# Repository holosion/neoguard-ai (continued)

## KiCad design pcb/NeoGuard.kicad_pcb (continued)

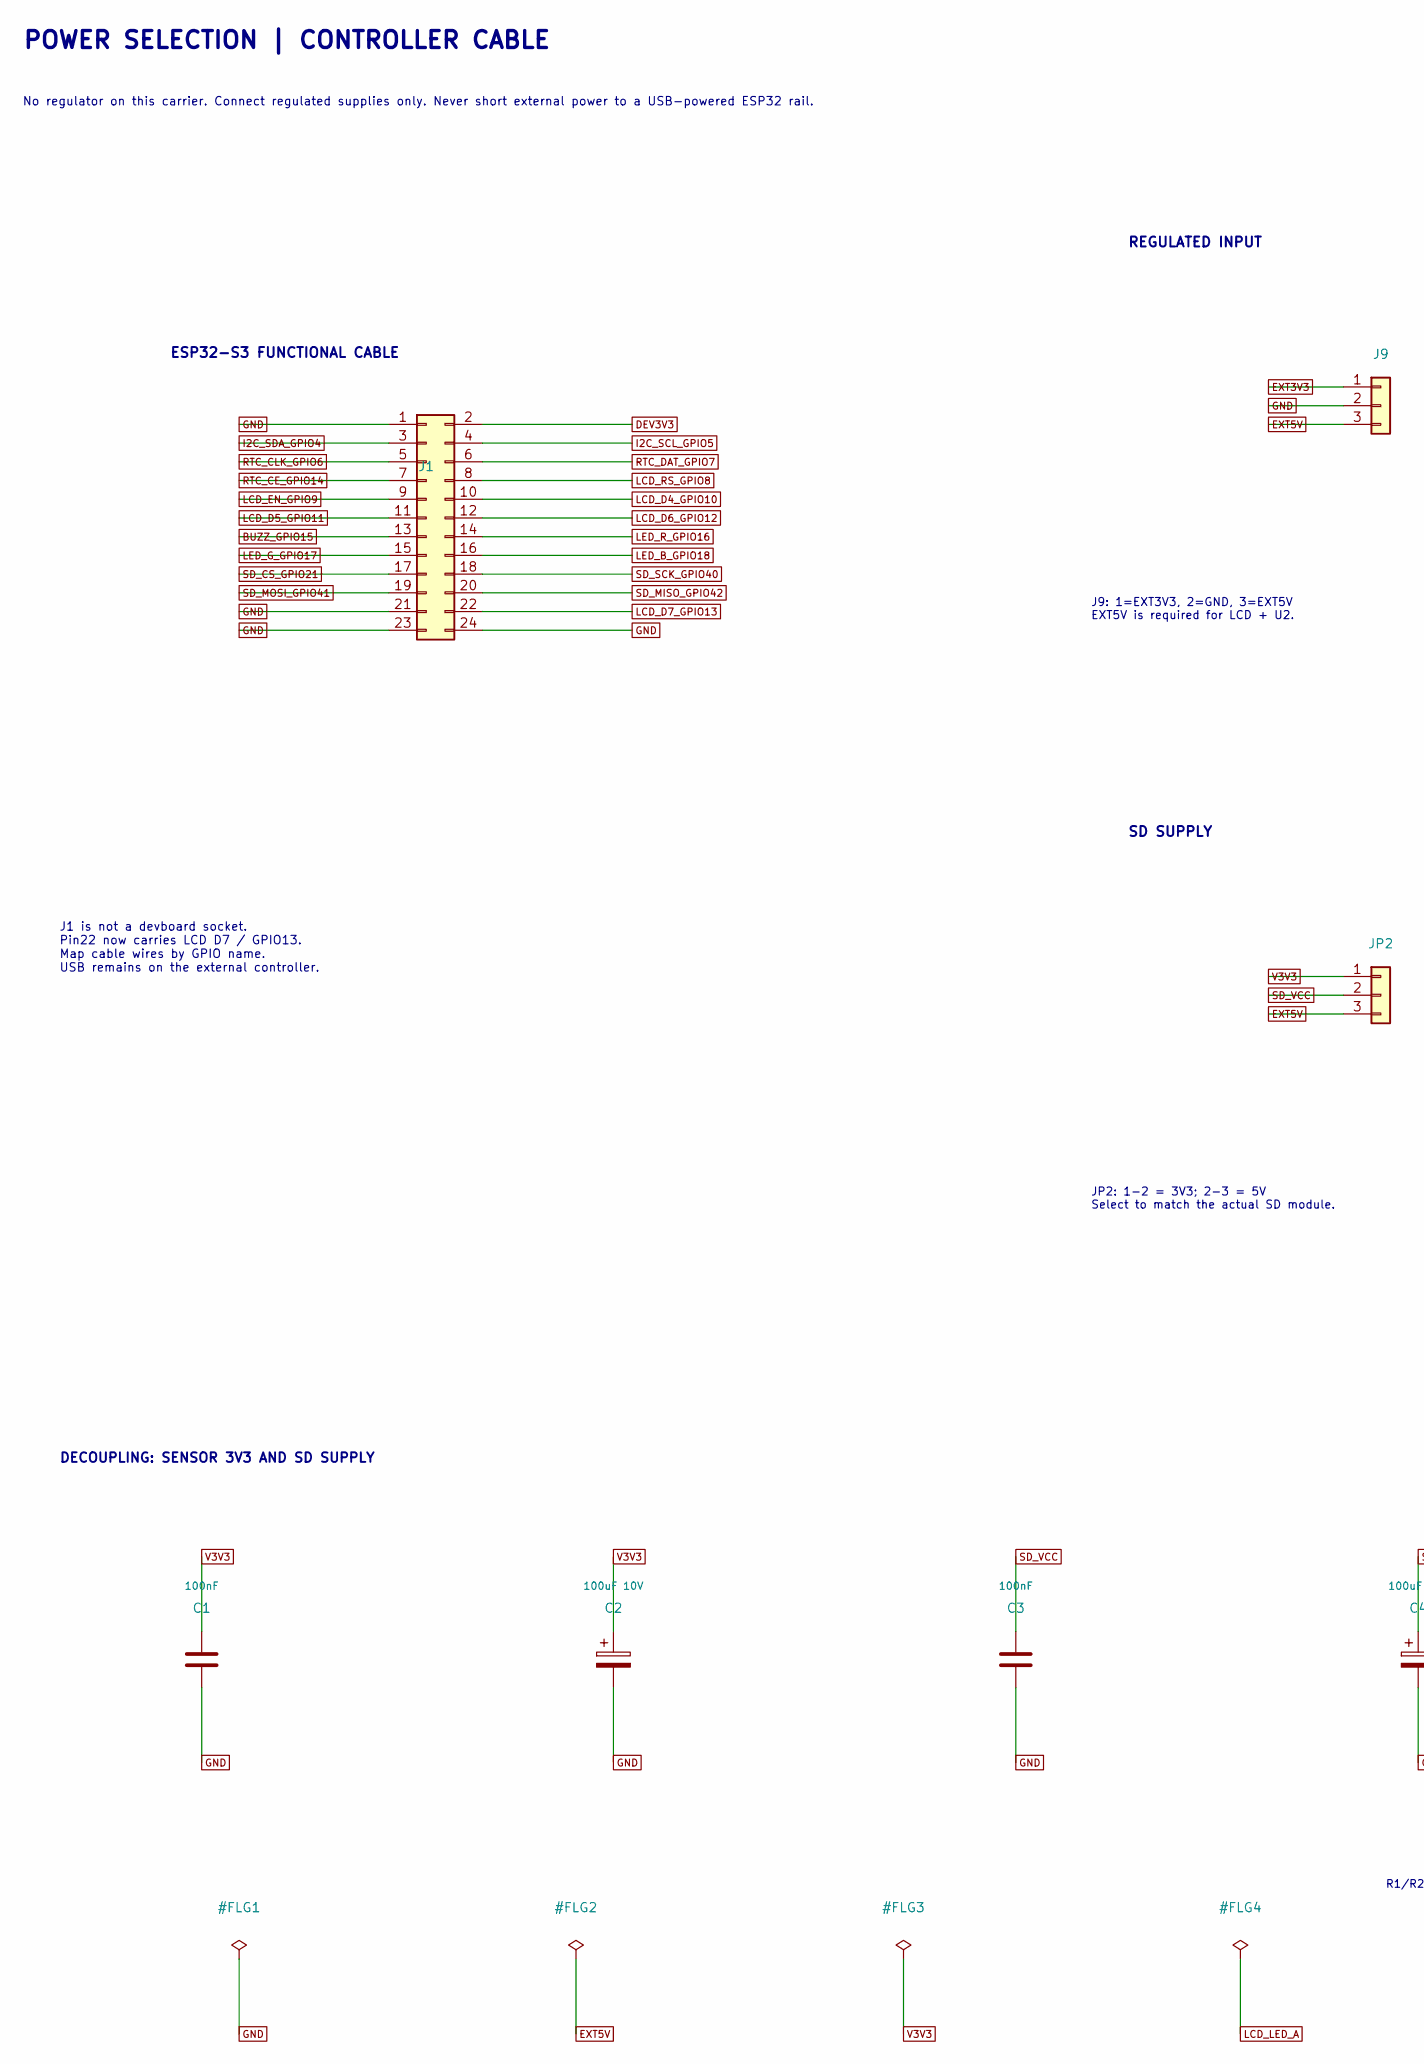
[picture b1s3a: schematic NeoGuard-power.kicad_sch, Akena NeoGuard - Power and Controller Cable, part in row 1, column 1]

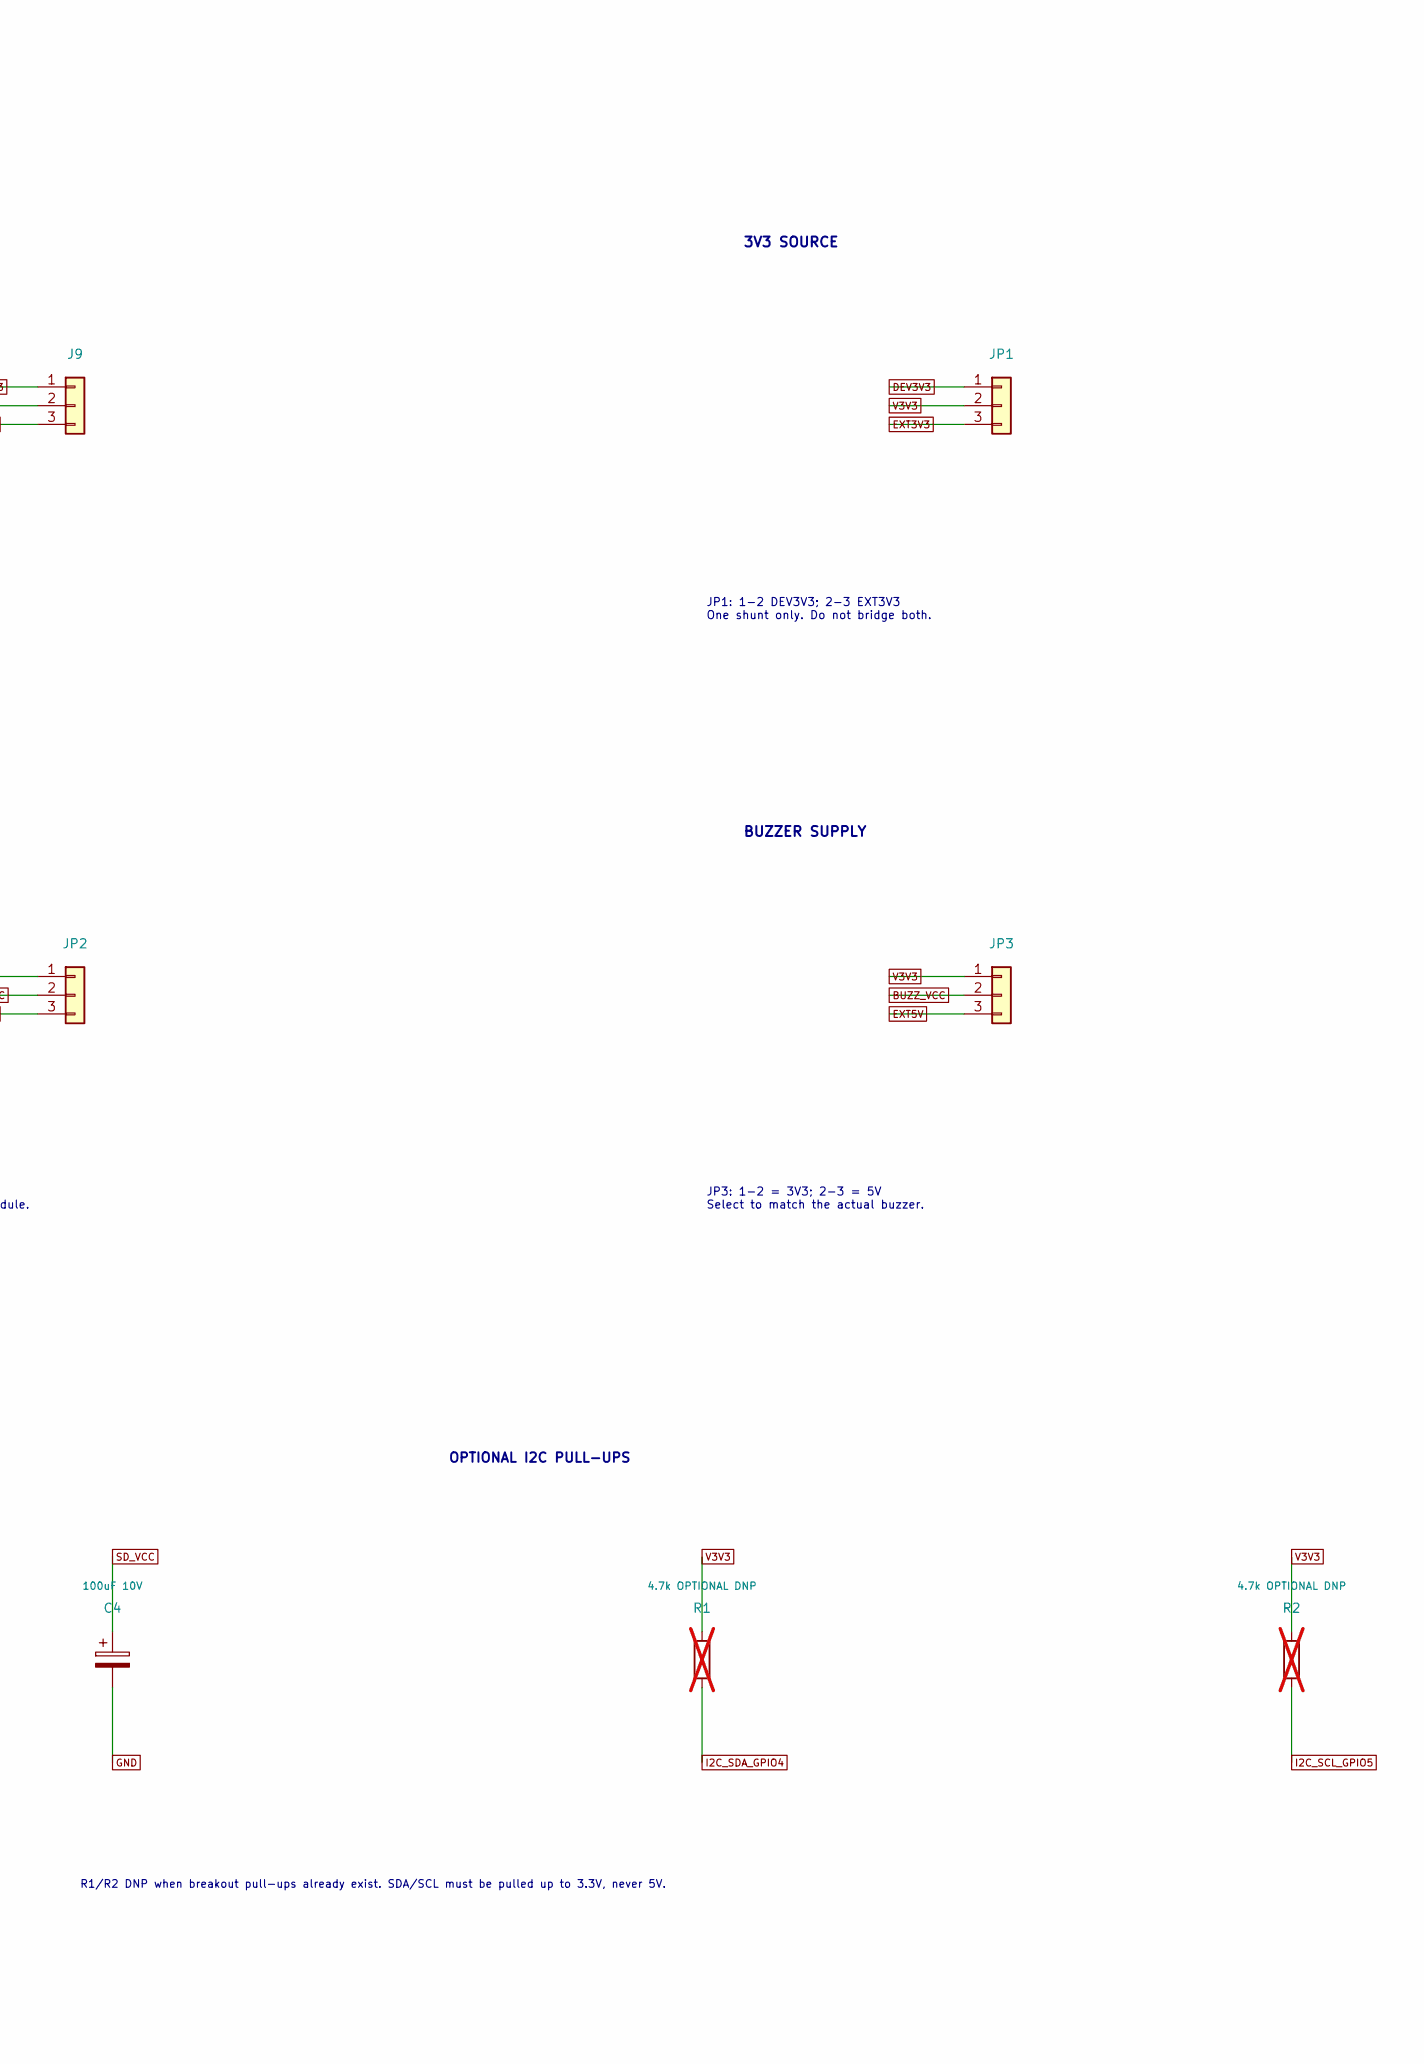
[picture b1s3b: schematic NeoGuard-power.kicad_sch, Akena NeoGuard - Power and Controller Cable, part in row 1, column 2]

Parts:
C1, C3: 100nF; C_Disc_D5.0mm_W2.5mm_P5.00mm
C2, C4: 100uF 10V; CP_Radial_D6.3mm_P2.50mm
J1: ESP32-S3 CABLE - NOT DEVBOARD SOCKET; PinHeader_2x12_P2.54mm_Vertical
J9: EXTERNAL REGULATED SUPPLIES; PinHeader_1x03_P2.54mm_Vertical
JP1: 3V3 SOURCE - ONE SHUNT; PinHeader_1x03_P2.54mm_Vertical
JP2: SD VOLTAGE - ONE SHUNT; PinHeader_1x03_P2.54mm_Vertical
JP3: BUZZ VOLTAGE - ONE SHUNT; PinHeader_1x03_P2.54mm_Vertical
R1, R2: 4.7k OPTIONAL DNP; R_Axial_DIN0207_L6.3mm_D2.5mm_P10.16mm_Horizontal; not fitted

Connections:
BUZZ_GPIO15: J1.13; also elsewhere on the board
BUZZ_VCC: JP3.2; also elsewhere on the board
DEV3V3: J1.2, JP1.1
EXT3V3: J9.1, JP1.3
EXT5V: J9.3, JP2.3, JP3.3; also elsewhere on the board
GND: C1.2, C2.2, C3.2, C4.2, J1.1, J1.21, J1.23, J1.24, J9.2; also elsewhere on the board
I2C_SCL_GPIO5: J1.4, R2.2; also elsewhere on the board
I2C_SDA_GPIO4: J1.3, R1.2; also elsewhere on the board
LCD_D4_GPIO10: J1.10; also elsewhere on the board
LCD_D5_GPIO11: J1.11; also elsewhere on the board
LCD_D6_GPIO12: J1.12; also elsewhere on the board
LCD_D7_GPIO13: J1.22; also elsewhere on the board
LCD_EN_GPIO9: J1.9; also elsewhere on the board
LCD_RS_GPIO8: J1.8; also elsewhere on the board
LED_B_GPIO18: J1.16; also elsewhere on the board
LED_G_GPIO17: J1.15; also elsewhere on the board
LED_R_GPIO16: J1.14; also elsewhere on the board
RTC_CE_GPIO14: J1.7; also elsewhere on the board
RTC_CLK_GPIO6: J1.5; also elsewhere on the board
RTC_DAT_GPIO7: J1.6; also elsewhere on the board
SD_CS_GPIO21: J1.17; also elsewhere on the board
SD_MISO_GPIO42: J1.20; also elsewhere on the board
SD_MOSI_GPIO41: J1.19; also elsewhere on the board
SD_SCK_GPIO40: J1.18; also elsewhere on the board
SD_VCC: C3.1, C4.1, JP2.2; also elsewhere on the board
V3V3: C1.1, C2.1, JP1.2, JP2.1, JP3.1, R1.1, R2.1; also elsewhere on the board

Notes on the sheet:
POWER SELECTION | CONTROLLER CABLE
No regulator on this carrier. Connect regulated supplies only. Never short external power to a USB-powered ESP32 rail.
ESP32-S3 FUNCTIONAL CABLE
REGULATED INPUT
3V3 SOURCE
SD SUPPLY
BUZZER SUPPLY
J1 is not a devboard socket. Pin22 now carries LCD D7 / GPIO13. Map cable wires by GPIO name. USB remains on the external controller.
J9: 1=EXT3V3, 2=GND, 3=EXT5V EXT5V is required for LCD + U2.
JP1: 1-2 DEV3V3; 2-3 EXT3V3 One shunt only. Do not bridge both.
JP2: 1-2 = 3V3; 2-3 = 5V Select to match the actual SD module.
JP3: 1-2 = 3V3; 2-3 = 5V Select to match the actual buzzer.
DECOUPLING: SENSOR 3V3 AND SD SUPPLY
OPTIONAL I2C PULL-UPS
R1/R2 DNP when breakout pull-ups already exist. SDA/SCL must be pulled up to 3.3V, never 5V.

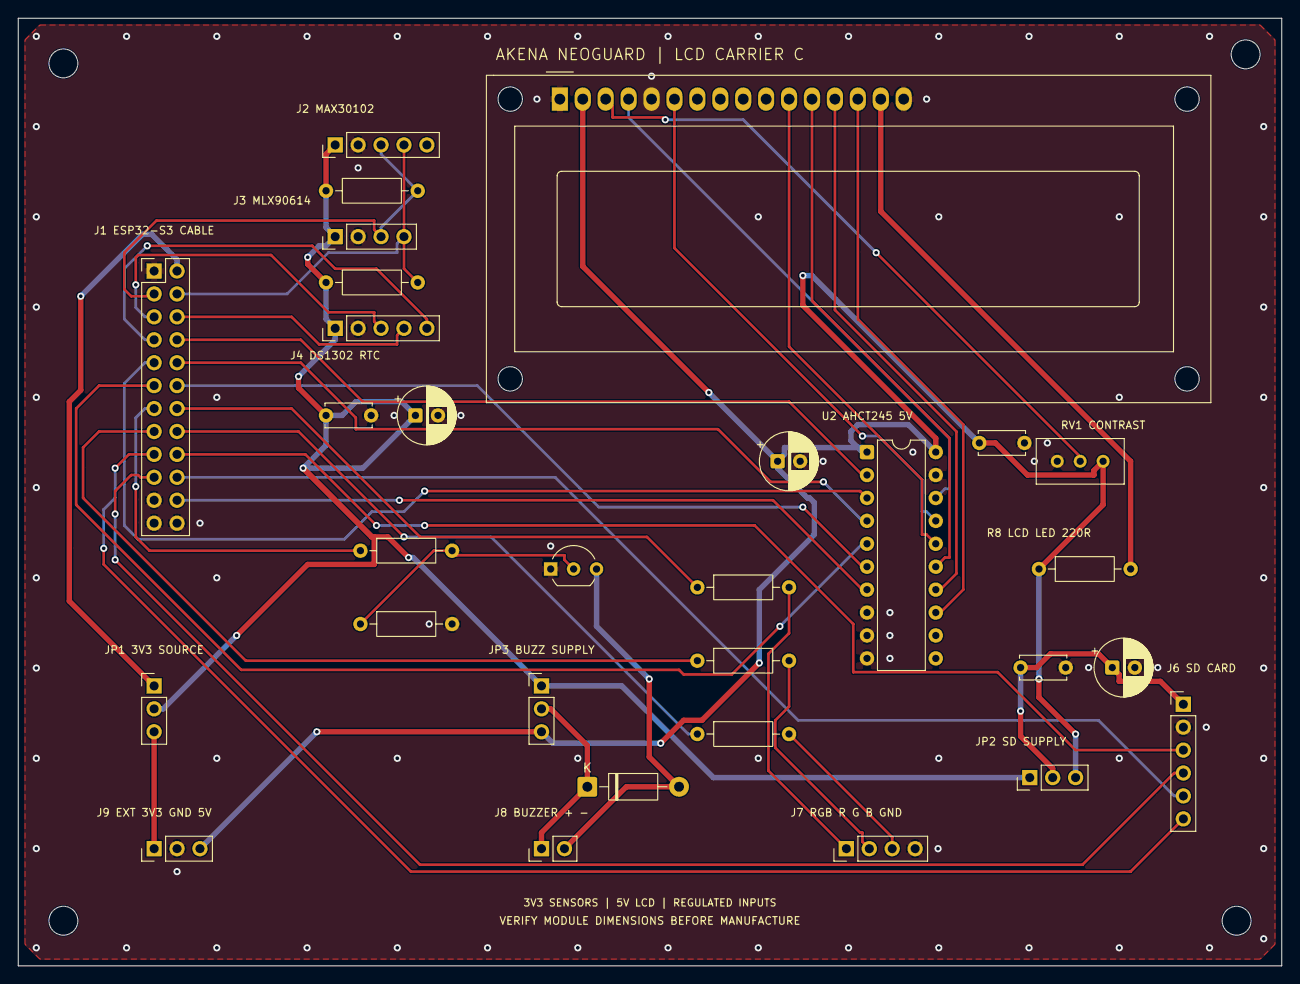
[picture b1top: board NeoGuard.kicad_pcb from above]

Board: 2 copper layers, 140.0 x 105.0 mm, 34 parts (0 on the bottom side), 39 nets.

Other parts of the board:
H1, H2, H3, H4: M3 3.2mm NPTH; MountingHole_3.2mm_M3

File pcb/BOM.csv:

Reference,Value,Footprint,Fit
J1,ESP32-S3 CABLE - NOT DEVBOARD SOCKET,Connector_PinHeader_2.54mm:PinHeader_2x12_P2.54mm_Vertical,FIT
J2,MAX30102 BREAKOUT,Connector_PinHeader_2.54mm:PinHeader_1x05_P2.54mm_Vertical,FIT
J3,MLX90614 3V3 BREAKOUT,Connector_PinHeader_2.54mm:PinHeader_1x04_P2.54mm_Vertical,FIT
J4,DS1302 MODULE,Connector_PinHeader_2.54mm:PinHeader_1x05_P2.54mm_Vertical,FIT
J5,WC1602A LCD 16x2 - VERIFY ACTUAL MODULE,Akena_LCD:LCD1602_80x36_Mounting,FIT
J6,SPI MICROSD MODULE,Connector_PinHeader_2.54mm:PinHeader_1x06_P2.54mm_Vertical,FIT
J7,EXTERNAL RGB COMMON CATHODE,Connector_PinHeader_2.54mm:PinHeader_1x04_P2.54mm_Vertical,FIT
J8,ACTIVE BUZZER 20mA MAX,Connector_PinHeader_2.54mm:PinHeader_1x02_P2.54mm_Vertical,FIT
J9,EXTERNAL REGULATED SUPPLIES,Connector_PinHeader_2.54mm:PinHeader_1x03_P2.54mm_Vertical,FIT
JP1,3V3 SOURCE - ONE SHUNT,Connector_PinHeader_2.54mm:PinHeader_1x03_P2.54mm_Vertical,FIT
JP2,SD VOLTAGE - ONE SHUNT,Connector_PinHeader_2.54mm:PinHeader_1x03_P2.54mm_Vertical,FIT
JP3,BUZZ VOLTAGE - ONE SHUNT,Connector_PinHeader_2.54mm:PinHeader_1x03_P2.54mm_Vertical,FIT
R1,4.7k OPTIONAL DNP,Resistor_THT:R_Axial_DIN0207_L6.3mm_D2.5mm_P10.16mm_Horizontal,DNP
R2,4.7k OPTIONAL DNP,Resistor_THT:R_Axial_DIN0207_L6.3mm_D2.5mm_P10.16mm_Horizontal,DNP
R3,330,Resistor_THT:R_Axial_DIN0207_L6.3mm_D2.5mm_P10.16mm_Horizontal,FIT
R4,330,Resistor_THT:R_Axial_DIN0207_L6.3mm_D2.5mm_P10.16mm_Horizontal,FIT
R5,330,Resistor_THT:R_Axial_DIN0207_L6.3mm_D2.5mm_P10.16mm_Horizontal,FIT
R6,1k,Resistor_THT:R_Axial_DIN0207_L6.3mm_D2.5mm_P10.16mm_Horizontal,FIT
R7,10k,Resistor_THT:R_Axial_DIN0207_L6.3mm_D2.5mm_P10.16mm_Horizontal,FIT
Q1,PN2222A E1 B2 C3,Package_TO_SOT_THT:TO-92_Inline_Wide,FIT
D1,1N5819,Diode_THT:D_DO-41_SOD81_P10.16mm_Horizontal,FIT
C1,100nF,Capacitor_THT:C_Disc_D5.0mm_W2.5mm_P5.00mm,FIT
C2,100uF 10V,Capacitor_THT:CP_Radial_D6.3mm_P2.50mm,FIT
C3,100nF,Capacitor_THT:C_Disc_D5.0mm_W2.5mm_P5.00mm,FIT
C4,100uF 10V,Capacitor_THT:CP_Radial_D6.3mm_P2.50mm,FIT
U2,SN74AHCT245N - NOT 74HC245,Package_DIP:DIP-20_W7.62mm,FIT
RV1,10k LCD CONTRAST,Potentiometer_THT:Potentiometer_Bourns_3296W_Vertical,FIT
R8,220 LCD BACKLIGHT,Resistor_THT:R_Axial_DIN0207_L6.3mm_D2.5mm_P10.16mm_Horizontal,FIT
C5,100nF U2 BYPASS,Capacitor_THT:C_Disc_D5.0mm_W2.5mm_P5.00mm,FIT
C6,10uF 10V LCD,Capacitor_THT:CP_Radial_D6.3mm_P2.50mm,FIT

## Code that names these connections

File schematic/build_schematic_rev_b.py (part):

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    custom_module(name,w,t,b,[(n,pn,round(snap(y)-snap(yy),4)) for n,pn,yy in pins],side)

GPINS=[
 ('4','GPIO4 / SDA',147.38,70,0,'bidirectional'),('5','GPIO5 / SCL',147.38,75,0,'bidirectional'),
 ('6','GPIO6 / CLK',147.38,147,0,'output'),('7','GPIO7 / DAT',147.38,152,0,'bidirectional'),('14','GPIO14 / CE',147.38,157,0,'output'),
 ('16','GPIO16 / RED',147.38,195,0,'output'),('17','GPIO17 / GREEN',147.38,200,0,'output'),('18','GPIO18 / BLUE',147.38,205,0,'output'),
 ('8','GPIO8 / RST',232.62,60,180,'output'),('9','GPIO9 / DC',232.62,65,180,'output'),('10','GPIO10 / CS',232.62,70,180,'output'),('11','GPIO11 / MOSI',232.62,75,180,'output'),('12','GPIO12 / SCK',232.62,80,180,'output'),
 ('21','GPIO21 / CS',232.62,120,180,'output'),('40','GPIO40 / SCK',232.62,125,180,'output'),('41','GPIO41 / MOSI',232.62,130,180,'output'),('42','GPIO42 / MISO',232.62,135,180,'input'),
 ('15','GPIO15 / BUZZ',232.62,200,180,'output'),('3V3','3V3 OUT',175,40.38,270,'passive'),('GND','GND',190,232.62,90,'passive')
]
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u1ps=[]
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main.place('R6',260,200,90,showval=True);main.place('Q1',295,200);main.place('R7',280,215,showval=True);main.place('D1',320,177.5,270)
main.wire(main.p('U1','15'),main.p('R6',1));main.pathwire(main.p('R6',2),(280,200),main.p('Q1',2));main.dot((280,200))
main.wire((280,200),main.p('R7',1))
main.wire((280,200),(280,191.77));main.label('BUZZ_BASE',(280,191.77),180)
main.pathwire(main.p('Q1',3),(main.p('Q1',3)[0],185),main.p('J8',2));main.dot((320,185))
main.pathwire(main.p('D1',2),(320,185));main.label('BUZZ_SW',main.p('J8',2),180)
main.pathwire(main.p('D1',1),(320,175),main.p('J8',1));main.dot((320,175));main.label('BUZZ_VCC',(320,175),180)
main.pathwire(main.p('Q1',1),(main.p('Q1',1)[0],225),(280,225),main.p('R7',2));main.label('GND',(280,225),0)
main.text('Q1 PN2222A: E1 / B2 / C3\nD1 1N5819: stripe/cathode toward buzzer +\nActive-high driver; buzzer 20 mA maximum.',250,231,1)
main.text('Selected V3V3 powers the modules; it is chosen on sheet 2. DEV3V3 is the controller output, not a short to external 3V3.',15,271,1)
main.text('Default screen is the working ST7789 TFT. A different OLED needs its own verified interface. GPIO40-42 must be available on the actual board.',15,277,1)
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
power=Page('power','/'+RID+'/'+SID)
power.text('NEOGUARD | POWER AND CARRIER HARNESS',15,14,2.3,True)
power.text('This sheet preserves the real carrier connector pin numbers and the selectable supply topology.',15,22,1.15)
power.text('J1 / CONTROLLER CABLE',20,36,1.5,True);power.place('J1',75,66,autolabel=True)
power.text('J1 is a cable connector, not a devboard socket.\nMap each pin to the GPIO label on U1 / sheet 1.\nPin 2 is DEV3V3 from the ESP32 board.\nPins 1 and 21-24 are common ground returns.',20,108,1.1)
power.text('INPUT SUPPLIES',170,36,1.5,True);power.place('J9',205,55,autolabel=True)
power.text('J9 accepts already regulated supplies:\n1 = external 3V3; 2 = GND; 3 = external 5V.\nNo onboard regulator or reverse-polarity protection.',165,81,1.1)
power.text('JP1 / CARRIER 3V3 SOURCE',285,36,1.5,True);power.place('JP1',330,55,autolabel=True)
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
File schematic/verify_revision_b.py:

"""Independent pin/net checks. Run with the Python supplied with KiCad 10."""
from pathlib import Path
import json
import xml.etree.ElementTree as ET
import pcbnew as pcb

root = Path(__file__).resolve().parent
manifest = json.loads((root / 'design_manifest.json').read_text())
xml = ET.parse(root / 'NeoGuard.net.xml')
nodes = {(n.attrib['ref'], n.attrib['pin']): net.attrib['name']
         for net in xml.findall('.//nets/net') for n in net.findall('node')}
clean = lambda value: value.lstrip('/') if value else value
expected_u1 = {
    '4': 'I2C_SDA_GPIO4', '5': 'I2C_SCL_GPIO5',
    '6': 'RTC_CLK_GPIO6', '7': 'RTC_DAT_GPIO7', '14': 'RTC_CE_GPIO14',
    '8': 'TFT_RST_GPIO8', '9': 'TFT_DC_GPIO9', '10': 'TFT_CS_GPIO10',
    '11': 'TFT_MOSI_GPIO11', '12': 'TFT_SCK_GPIO12',
    '21': 'SD_CS_GPIO21', '40': 'SD_SCK_GPIO40',
    '41': 'SD_MOSI_GPIO41', '42': 'SD_MISO_GPIO42',
    '15': 'BUZZ_GPIO15', '16': 'LED_R_GPIO16',
    '17': 'LED_G_GPIO17', '18': 'LED_B_GPIO18',
    '3V3': 'DEV3V3', 'GND': 'GND',
}
for part in manifest['components']:
    for pin, net in part['pins'].items():
        if net is not None:
            actual = clean(nodes.get((part['ref'], pin)))
            assert actual == net, ('schematic', part['ref'], pin, net, actual)
for pin, net in expected_u1.items():
    assert clean(nodes.get(('U1', pin))) == net, ('U1', pin, net, nodes.get(('U1', pin)))
u1 = next(c for c in xml.findall('.//components/comp') if c.get('ref') == 'U1')
u1_properties = {p.get('name'): p.get('value') for p in u1.findall('property')}
assert 'exclude_from_board' in u1_properties, u1_properties
assert clean(nodes[('U1', '3V3')]) != clean(nodes[('J2', '1')]), 'Power selector bypassed'

board = pcb.LoadBoard(str(root / 'NeoGuard.kicad_pcb'))
parts = {f.GetReference(): f for f in board.GetFootprints()}
assert 'U1' not in parts, 'Offboard controller incorrectly added to PCB'
pad_count = 0
for part in manifest['components']:
    assert part['ref'] in parts
    pads = {p.GetNumber(): p for p in parts[part['ref']].Pads()}
    for number, net in part['pins'].items():
        pad_count += 1
        assert number in pads
        actual = clean(pads[number].GetNetname())
        if net is None:
            assert not actual or actual.startswith('unconnected-'), (part['ref'], number, actual)
        else:
            assert actual == net, ('PCB', part['ref'], number, net, actual)
assert pad_count == 99
assert board.GetCopperLayerCount() == 2
zone_data = []
for zone in board.Zones():
    assert zone.GetNetname() == 'GND'
    assert zone.GetPadConnection() == pcb.ZONE_CONNECTION_THERMAL
    area = zone.GetFilledPolysList(zone.GetLayer()).Area() / 1e12
    assert area > 10000, ('Empty or unexpectedly fragmented ground zone', area)
    zone_data.append({'layer': board.GetLayerName(zone.GetLayer()), 'filled_area_mm2': round(area, 2)})
assert {z['layer'] for z in zone_data} == {'F.Cu', 'B.Cu'}
ground_vias = [t for t in board.GetTracks() if isinstance(t, pcb.PCB_VIA) and t.GetNetname() == 'GND']
assert len(ground_vias) >= 20
erc = json.loads((root / 'ERC.json').read_text())
drc = json.loads((root / 'pcb_drc.json').read_text())
assert not any(s.get('violations') for s in erc['sheets'])
assert not drc['violations'] and not drc['unconnected_items'] and not drc['schematic_parity']
result = {'revision': 'B', 'carrier_pad_checks': pad_count, 'controller_pin_checks': len(expected_u1),
          'carrier_net_mismatches': 0, 'controller_net_mismatches': 0,
          'copper_layers': board.GetCopperLayerCount(), 'ground_vias': len(ground_vias),
          'ground_zones': zone_data, 'erc_violations': 0, 'drc_violations': 0,
          'unconnected_items': 0, 'schematic_parity_issues': 0}
(root / 'verification_summary.json').write_text(json.dumps(result, indent=2) + '\n')
print(json.dumps(result, indent=2))

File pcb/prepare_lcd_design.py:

"""Create the LCD revision without modifying the earlier TFT project."""
from pathlib import Path
import json, shutil, re

ROOT = Path(__file__).resolve().parent
OLD = ROOT.parent / 'schematic'
m = json.loads((OLD/'design_manifest.json').read_text())
m.update(revision='LCD-C', date='2026-10-22', design_type='LCD module carrier; controller on functional cable header; mechanical fit unconfirmed')
rename = dict(zip(['TFT_RST_GPIO8','TFT_DC_GPIO9','TFT_CS_GPIO10','TFT_MOSI_GPIO11','TFT_SCK_GPIO12'], ['LCD_RS_GPIO8','LCD_EN_GPIO9','LCD_D4_GPIO10','LCD_D5_GPIO11','LCD_D6_GPIO12']))
m['components'] = [c for c in m['components'] if c['ref'] != 'JP4']
for c in m['components']:
    c['pins'] = {k:rename.get(v,v) for k,v in c['pins'].items()}
cm = {c['ref']:c for c in m['components']}
cm['J1']['pins']['22'] = 'LCD_D7_GPIO13'
cm['J5'].update(value='WC1602A LCD 16x2 - VERIFY ACTUAL MODULE', symbol='Display_Character:WC1602A', footprint='Display:WC1602A', pins={str(i):n for i,n in enumerate(['GND','EXT5V','LCD_CONTRAST','LCD_RS_5V','GND','LCD_EN_5V',None,None,None,None,'LCD_D4_5V','LCD_D5_5V','LCD_D6_5V','LCD_D7_5V','LCD_LED_A','GND'],1)})
def add(ref,value,symbol,footprint,pins):
    c=dict(ref=ref,value=value,symbol=symbol,footprint=footprint,pins={str(k):v for k,v in pins.items()});m['components'].append(c)
add('U2','SN74AHCT245N - NOT 74HC245','74xx:74HC245','Package_DIP:DIP-20_W7.62mm', {1:'EXT5V',2:'LCD_RS_GPIO8',3:'LCD_EN_GPIO9',4:'LCD_D4_GPIO10',5:'LCD_D5_GPIO11',6:'LCD_D6_GPIO12',7:'LCD_D7_GPIO13',8:'GND',9:'GND',10:'GND',11:None,12:None,13:'LCD_D7_5V',14:'LCD_D6_5V',15:'LCD_D5_5V',16:'LCD_D4_5V',17:'LCD_EN_5V',18:'LCD_RS_5V',19:'GND',20:'EXT5V'})
add('RV1','10k LCD CONTRAST','Device:R_Potentiometer','Potentiometer_THT:Potentiometer_Bourns_3296W_Vertical',{1:'EXT5V',2:'LCD_CONTRAST',3:'GND'})
add('R8','220 LCD BACKLIGHT','Device:R',cm['R3']['footprint'],{1:'EXT5V',2:'LCD_LED_A'})
add('C5','100nF U2 BYPASS','Device:C',cm['C1']['footprint'],{1:'EXT5V',2:'GND'})
add('C6','10uF 10V LCD','Device:C_Polarized',cm['C2']['footprint'],{1:'EXT5V',2:'GND'})
(ROOT/'design_manifest.json').write_text(json.dumps(m,indent=2))
shutil.copy2(OLD/'NeoGuard.kicad_pro', ROOT/'NeoGuard.kicad_pro')
shutil.copy2(OLD/'fp-lib-table', ROOT/'fp-lib-table')

# Retain the proven KiCad symbol parser and schematic writer, not old connectivity.
src=(OLD/'build_schematic_rev_b.py').read_text()
prefix=src[:src.index('# Absolute page coordinates')]
helpers=src[src.index('def pin_defs('):src.index("main=Page('main'")]
helpers=helpers.replace('2026-10-21','2026-10-22').replace('(rev "B")','(rev "LCD-C")')
helpers=helpers.replace("if ref=='U1':ry=43;vy=37", "if ref=='U1':ry=y-65;vy=y-70")
helpers=helpers.replace("ref!='U1'", "ref!='U1'")
helpers=helpers.replace('if ref=="U1" else', 'if ref=="U1" or ref.startswith("#") else')
controller='''
# Fixed-direction symbol for the hardwired A->B buffer; no bidirectional outputs on A.
buffer=LIBS.pop('74HC245')
rename(buffer,'74HC245','SN74AHCT245_AtoB');buffer[1]='SN74AHCT245_AtoB'
for sub in children(buffer,'symbol'):
 for pin in children(sub,'pin'):
  number=int(child(pin,'number')[1])
  if 2 <= number <= 9: pin[1]=Atom('input')
  elif 11 <= number <= 18: pin[1]=Atom('output')
LIBS['SN74AHCT245_AtoB']=buffer
CM['U2']['symbol']='NeoGuard:SN74AHCT245_AtoB'
U1NET = {'4':'I2C_SDA_GPIO4','5':'I2C_SCL_GPIO5','6':'RTC_CLK_GPIO6','7':'RTC_DAT_GPIO7','14':'RTC_CE_GPIO14','8':'LCD_RS_GPIO8','9':'LCD_EN_GPIO9','10':'LCD_D4_GPIO10','11':'LCD_D5_GPIO11','12':'LCD_D6_GPIO12','13':'LCD_D7_GPIO13','15':'BUZZ_GPIO15','16':'LED_R_GPIO16','17':'LED_G_GPIO17','18':'LED_B_GPIO18','21':'SD_CS_GPIO21','40':'SD_SCK_GPIO40','41':'SD_MOSI_GPIO41','42':'SD_MISO_GPIO42','3V3':'DEV3V3','GND':'GND'}
custom_module('ESP32_S3_Logical',45,60,-60,[(n,net.replace('_GPIO',' / GPIO'),55.88-i*5.08) for i,(n,net) in enumerate(U1NET.items())])
'''
(ROOT/'build_schematic.py').write_text(prefix+controller+helpers+(ROOT/'schematic_pages.py.txt').read_text())

# Place the module and its real 3D model, then route once using the existing router.
base=(OLD/'build_pcb.py').read_text()
base=base[base.index('import json'):base.index('# Compact labels')]
a=base.index("if __name__=='__main__'");b=base.index('M = json.loads',a)
base=base[:a]+base[b:]
base=base.replace("'J2':(64.008,34.036,90)","'J2':(55.118,34.036,90)")
base=base.replace("'J3':(83.058,34.036,90)","'J3':(55.118,44.196,90)")
base=base.replace("'J4':(107.95,34.036,90)","'J4':(55.118,54.356,90)")
base=base.replace("'R1':(58.928,49.022,0)","'R1':(54.102,39.116,0)")
base=base.replace("'R2':(58.928,57.15,0)","'R2':(54.102,49.276,0)")
base=base.replace("'J5':(149.098,45.974,0)","'J5':(80.01,28.956,0)")
base=base.replace("'J6':(149.098,84.074,0)","'J6':(149.098,96.012,0)")
base=base.replace("'JP2':(132.08,91.948,0)","'JP2':(132.08,104.14,90)")
base=base.replace("'C1':(67.056,40.132,0)","'C1':(54.102,64.008,0)")
base=base.replace("'C2':(55.118,40.132,0)","'C2':(64.008,64.008,0)")
base=base.replace("'C3':(125.984,77.978,0)","'C3':(131.064,91.948,0)")
base=base.replace("'C4':(140.208,77.978,0)","'C4':(141.224,91.948,0), 'U2':(114.046,68.072,0), 'RV1':(140.208,69.088,0), 'R8':(133.096,81.026,0), 'C5':(126.492,67.056,0), 'C6':(104.14,69.088,0)")
base=base.replace('(155,25)','(156,24)')
base=base.replace("'ST7789 TFT'","'16x2 LCD ON BOARD'")
base=base.replace("'NEOGUARD  |  MODULE CARRIER  |  REV A'","'AKENA NEOGUARD  |  LCD CARRIER  |  REV C'")
base=base.replace("'FUNCTIONAL CABLE HEADERS - VERIFY MODULE PIN ORDER'","'REVIEW PROTOTYPE - VERIFY LCD / MODULE DIMENSIONS'")
base=base.replace("'3.3V LOGIC ONLY   |   NO ONBOARD REGULATOR'","'3V3 SENSORS  |  5V LCD VIA AHCT245  |  REGULATED INPUTS'")
base=base.replace("'ONE SHUNT ONLY ON EACH 3-PIN SELECTOR'","'ONE SHUNT PER SELECTOR - DO NOT BRIDGE USB AND EXT POWER'")
base=base.replace('max(.8,size)','max(.8,size)')
base+= '''
# Four dedicated LCD mounting holes. Their positions are an explicit WC1602A assumption.
for hole in byref['J5'].Pads():
 if not hole.GetNumber():
  hole.SetAttribute(p.PAD_ATTRIB_NPTH)
  hole.SetShape(p.PAD_SHAPE_CIRCLE);hole.SetSize(v(2.7,2.7));hole.SetDrillSize(v(2.7,2.7))
for fp in board.GetFootprints():
 fp.Reference().SetVisible(False)
for ref,label in {'J1':'ESP32-S3 CABLE','J2':'MAX30102','J3':'MLX90614','J4':'DS1302','J6':'SD CARD','J7':'RGB R G B GND','J8':'BUZZER + -','J9':'EXT 3V3 GND 5V','JP1':'3V3 SOURCE','JP2':'SD SUPPLY','JP3':'BUZZ SUPPLY','U2':'AHCT245 5V','RV1':'LCD CONTRAST','R8':'LCD LED 220R'}.items():
 x,y,r=POS[ref];text(ref+' '+label,x-2,y-4,0.85)
text('LCD1602: RS8 EN9 D4:10 D5:11 D6:12 D7:13',111,66,0.8)
text('LCD MOUNTING: WC1602A 80 x 36 mm ASSUMED',111,60,.8)
text('J1 IS A CABLE HEADER, NOT A DEVBOARD SOCKET',53,88,.8)
text('I2C SDA4 / SCL5',60,27,.85)
p.SaveBoard(str(ROOT/'NeoGuard.kicad_pcb'),board)
from route_lcd import run
run()
'''
(ROOT/'build_pcb.py').write_text(base)
route=(OLD/'refine_pcb_revision_b.py').read_text()
route=route.replace("'BUZZ_SW'}","'BUZZ_SW','LCD_LED_A'}")
route=route.replace('apply_paths(board);finish_silk_and_outline(board)','apply_paths(board)')
route=route.replace("SetRevision('B')","SetRevision('LCD-C')").replace('2026-10-21','2026-10-22')
route=route.replace('NeoGuard module carrier - thermal ground pours and 45-degree routing','Akena NeoGuard LCD carrier - mechanical assumptions unconfirmed')
(ROOT/'route_lcd.py').write_text(route)
print('Prepared LCD manifest, schematic generator and PCB builder.')
